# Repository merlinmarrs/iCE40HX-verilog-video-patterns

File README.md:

# Video FPGA Dev Board

A Lattice iCE40HX1K-based FPGA developement board for live-playable video experiments.

|                          |                          |
:-------------------------:|:-------------------------:
  | 

# Features :

- 9-key mechanical button interface
- Relatively low-cost, single board design
- HDMI and VGA out
- Reverse polarity and fuse protection

# Minimal BOM :

[Excel BOM Mouser / Digikey ](https://github.com/merlinmarrs/iCE40HX-verilog-video-patterns/tree/main/PCB%20files)

- 9x Mechanical keyboard keys
- 1x FPGA iCE40HX1K-TQ144
- 1x 100MHz clock oscillator
- 1x SRAM 2Mb 256Kx8
- 1x Flash N25Q032A13ESC40F
- 1x USB-C SMD 6 pin connector
- 1x 3.3V reg TLV73333PDBVT 
- 1x 1.2V reg TLV73312PDBVT
- 1x PFET
- 1x Resettable Fuse
- 1x D-SUB 15 connector
- 1x HDMI Connector 
- 50x 0.1µF capacitor 0805
- 50x  10kΩ, 1.8kΩ, 1kΩ, 470Ω, 270Ω, 120Ω resistors 0805
- 5x LEDs 0805
- 2x Dual-row headers

optional extras : (1x Raspberry Pi Zero, 1x Micro SD holder, 2x 10kΩ potentiometers, 1x fast op-amp, 1x 3.5mm audio jack, 1x dual SMD dip switch, 1x SMD pushbutton)

# PCB files

[KiCAD and Eagle PCBs](https://github.com/merlinmarrs/iCE40HX-verilog-video-patterns/tree/main/PCB%20files)

# HDL files

[Verilog, Pin constraints, and synthesized binaries ](https://github.com/merlinmarrs/iCE40HX-verilog-video-patterns/tree/main/verilog)

To compile and upload files :

[Yoysis Open-source Toolchain ](https://github.com/YosysHQ/yosys)

[iCEcube2 Toolchain](https://www.latticesemi.com/iCEcube2)

## Acknowledgements

Mike Field <hamster@snap.net.nz> for his minimalDVID_encoder.vhd : A quick and dirty DVI-D implementation

OLIMEX FPGA dev board https://github.com/OLIMEX/iCE40HX1K-EVB/tree/master

ALHAMBRA FPGA https://github.com/FPGAwars/Alhambra-II-FPGA/tree/master

HDL Bits https://hdlbits.01xz.net/wiki/Main_Page

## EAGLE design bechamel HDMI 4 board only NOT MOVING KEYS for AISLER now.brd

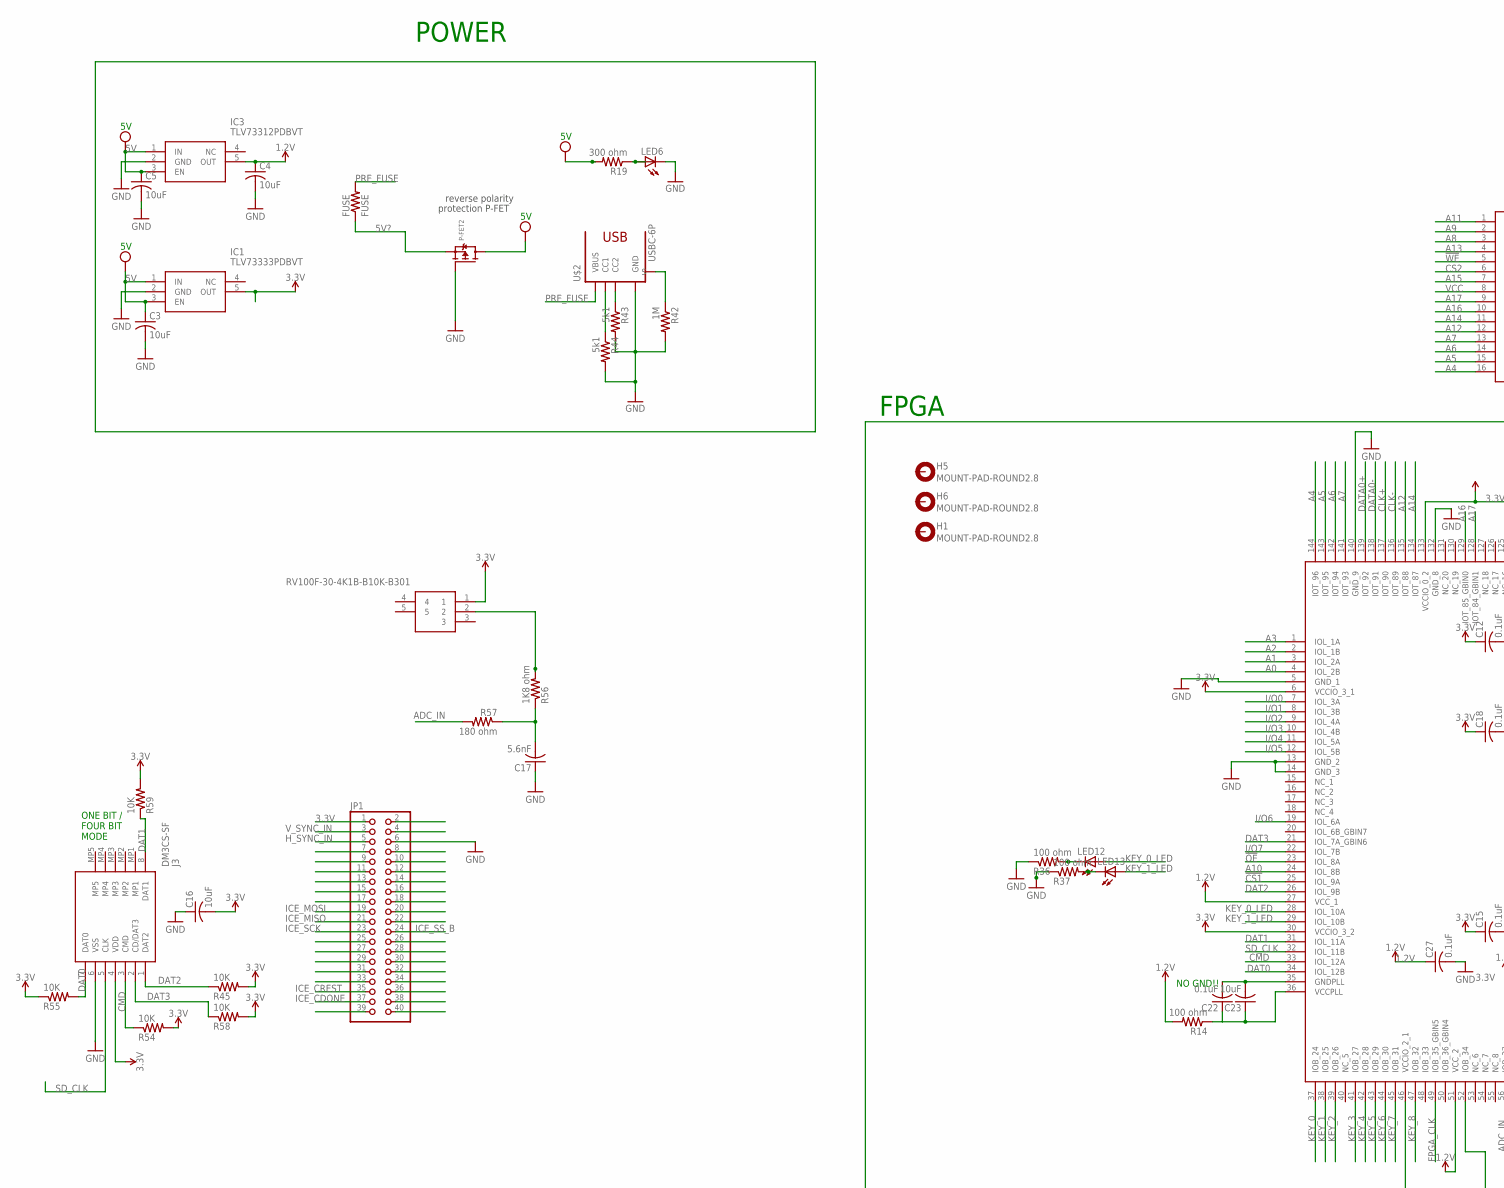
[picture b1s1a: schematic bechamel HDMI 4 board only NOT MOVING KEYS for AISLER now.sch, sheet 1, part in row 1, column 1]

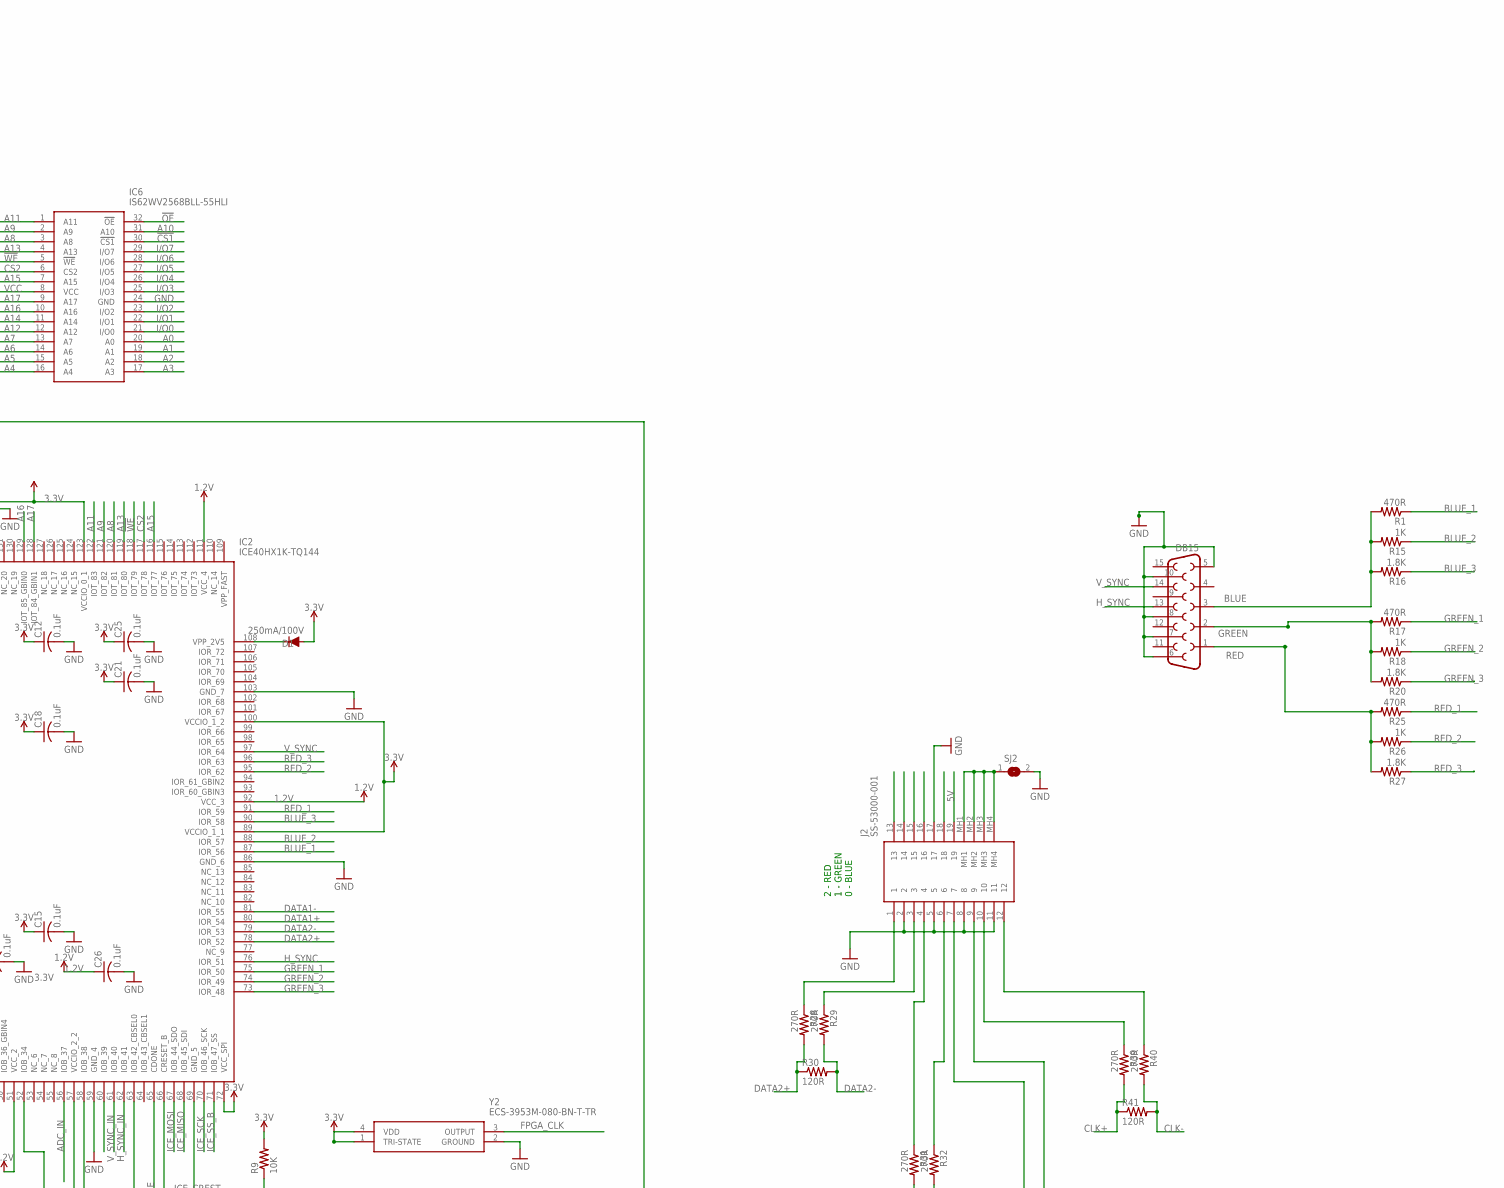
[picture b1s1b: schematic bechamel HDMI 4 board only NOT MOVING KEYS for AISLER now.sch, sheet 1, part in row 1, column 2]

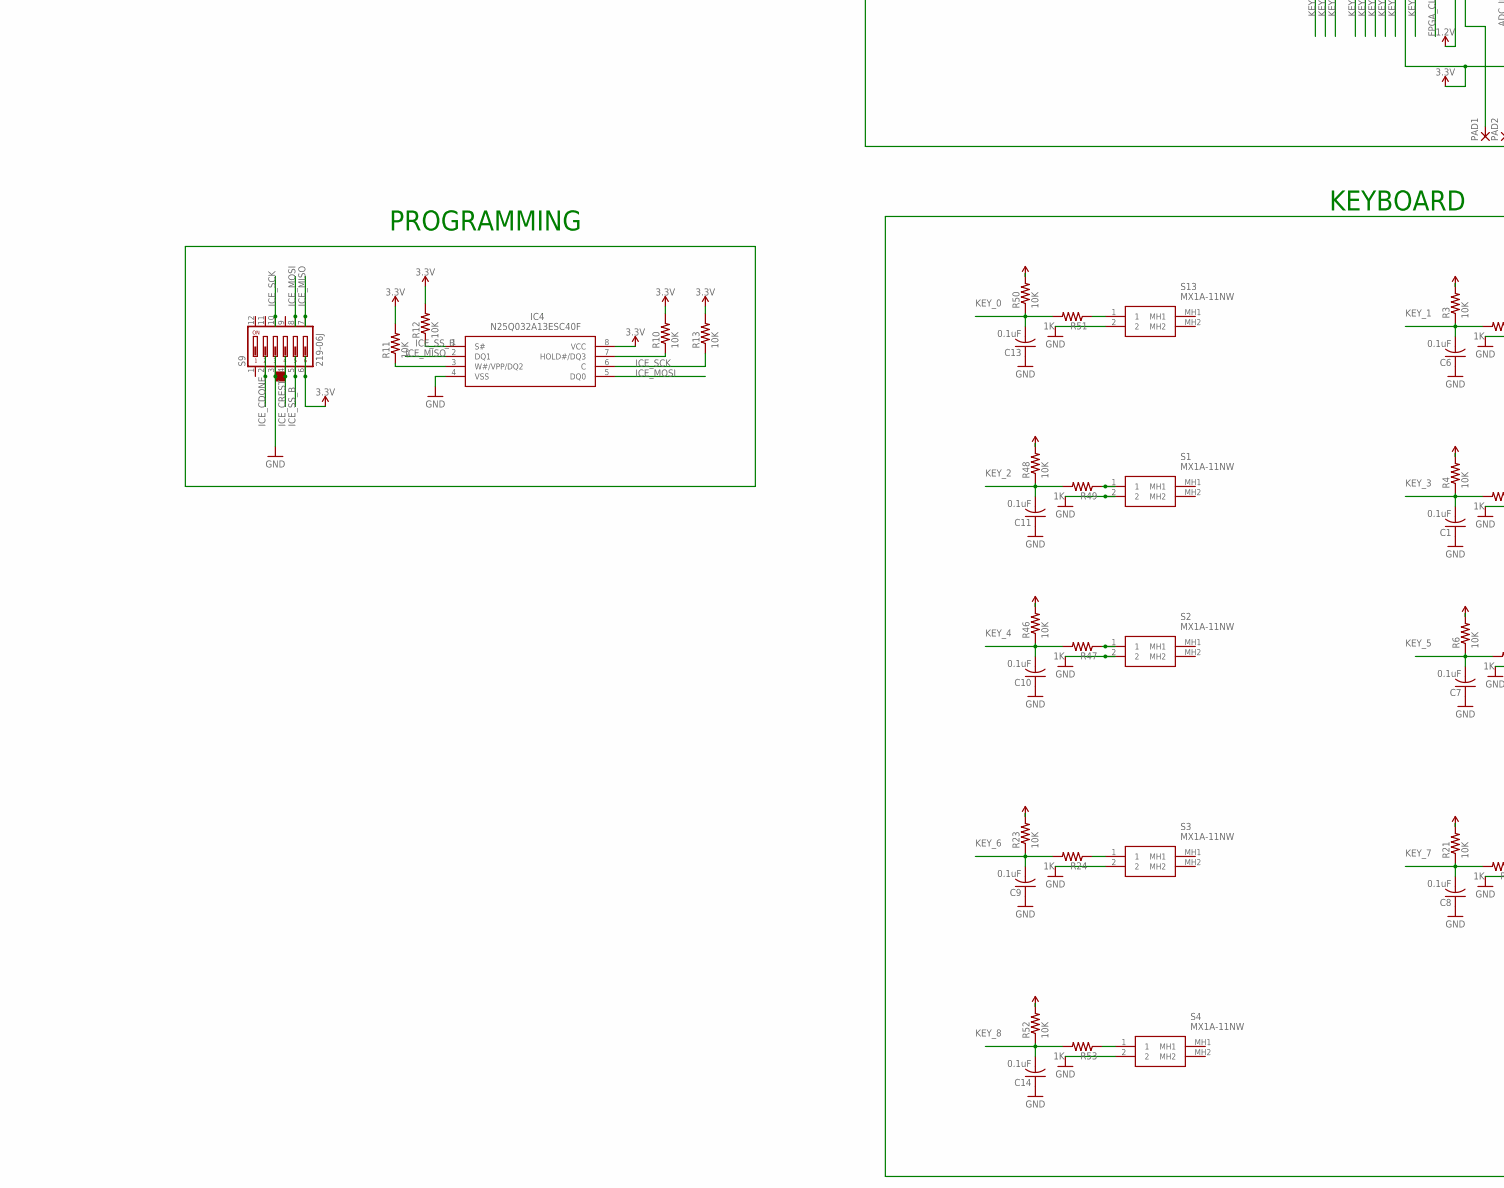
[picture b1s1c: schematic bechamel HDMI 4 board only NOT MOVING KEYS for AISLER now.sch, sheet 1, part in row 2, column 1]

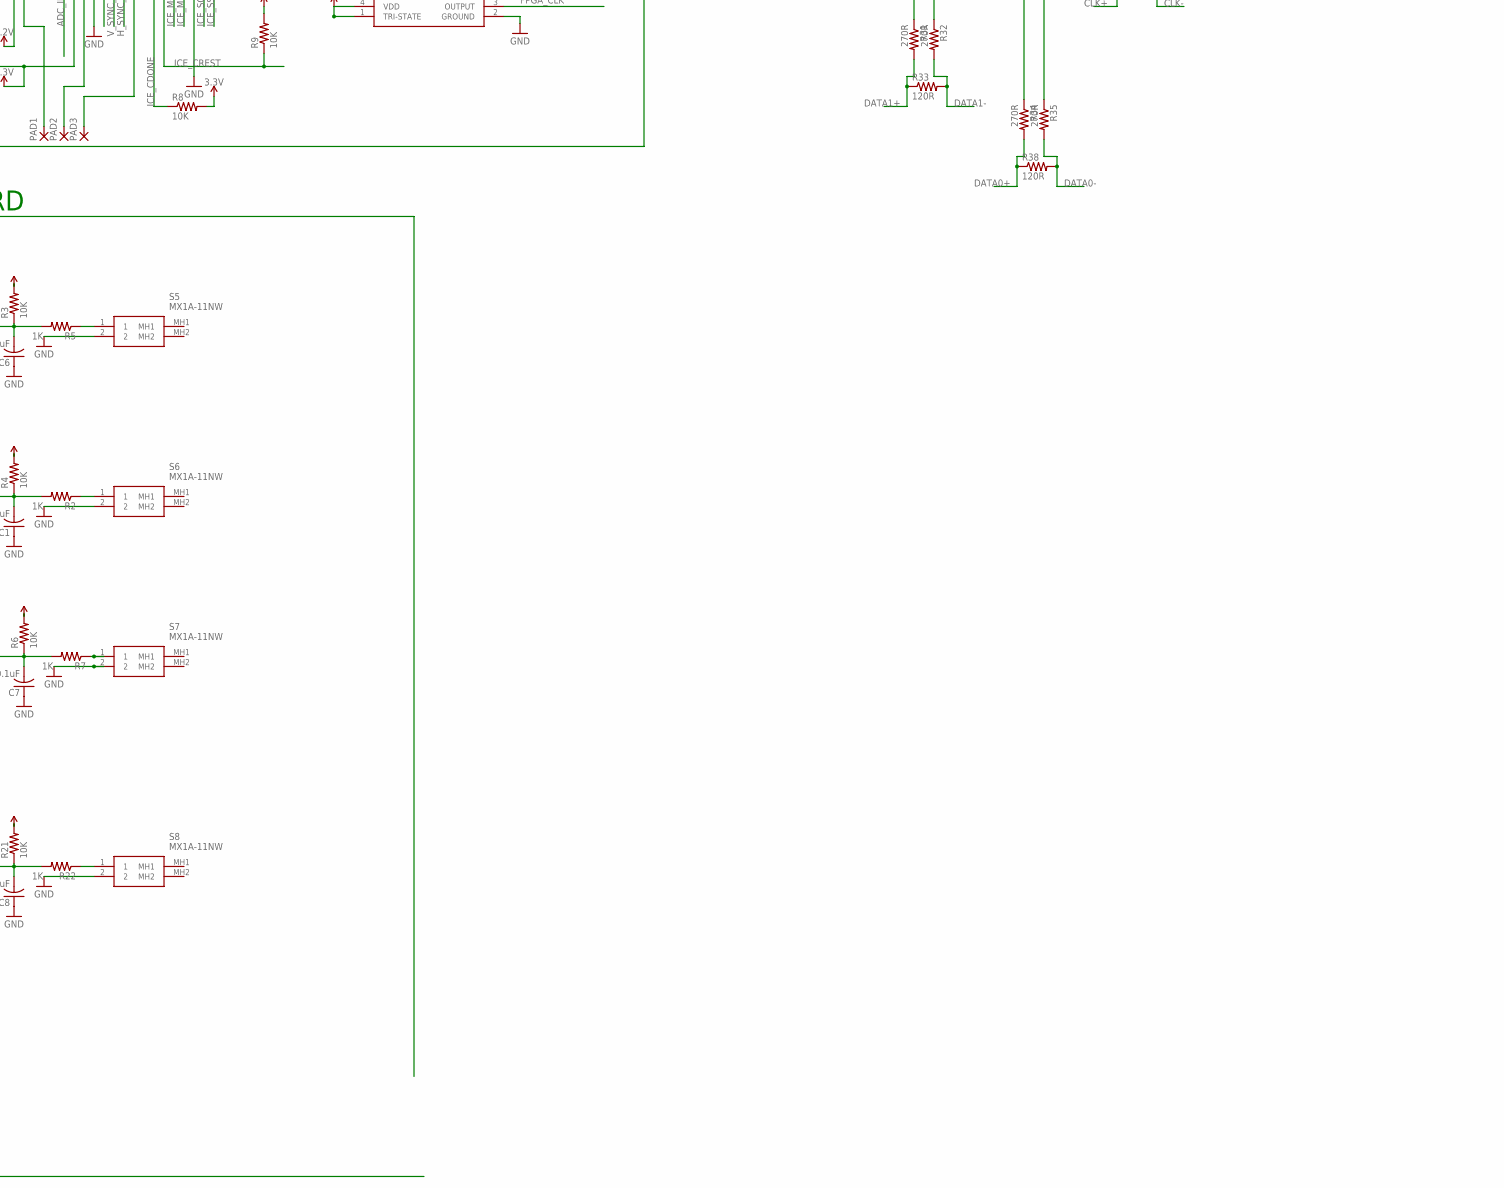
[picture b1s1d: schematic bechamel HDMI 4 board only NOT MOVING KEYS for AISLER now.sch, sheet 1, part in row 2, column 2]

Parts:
C1, C6, C7, C8, C9, C10, C11, C12, C13, C14, C15, C18, C21, C22, C25, C26, C27: 0.1uF; C0805
C3, C4, C5, C16, C23: 10uF; C0805
C17: 5.6nF; C0805
D1: 250mA/100V; SOD-323
FUSE: FUSE; R0805
H1, H5, H6: MOUNT-PAD-ROUND2.8; 2,8-PAD
IC1: TLV73333PDBVT; SOT95P280X145-5N
IC2: ICE40HX1K-TQ144; QFP50P2200X2200X160-144N
IC3: TLV73312PDBVT; SOT95P280X145-5N
IC4: N25Q032A13ESC40F; SOIC127P600X175-8N
IC6: IS62WV2568BLL-55HLI; SOP50P1340X125-32N
J2: SS-53000-001; SS53000001
J3: DM3CS-SF; DM3CSSF
JP1: PINHD-2X20; 2X20
LED6, LED12, LED13: LEDCHIPLED_0805; CHIPLED_0805
P-FET2: MOSFET-PWIDE; SOT23-WIDE
PAD1, PAD2, PAD3: SMD2; SMD1,27-2,54
R1, R17, R25: 470R; R0805
R2, R5, R7, R15, R18, R22, R24, R26, R47, R49, R51, R53: 1K; R0805
R3, R4, R6, R8, R9, R10, R11, R12, R13, R21, R23, R45, R46, R48, R50, R52, R54, R55, R58, R59: 10K; R0805
R14, R36, R37: 100 ohm; R0805
R16, R20, R27: 1.8K; R0805
R19: 300 ohm; R0805
R28, R29, R31, R32, R34, R35, R39, R40: 270R; R0805
R30, R33, R38, R41: 120R; R0805
R42: 1M; R0805
R43, R44: 5k1; R0805
R56: 1K8 ohm; R0805
R57: 180 ohm; R0805
S1, S2, S3, S4, S5, S6, S7, S8, S13: MX1A-11NW; MX1A11NW
S9: 219-06J; CTS-219-06J
SJ2: SJ
U$1: DB15
U$2: USBC-6P; USCX-06FX-XXMX-01
VR1: RV100F-30-4K1B-B10K-B301; RV100F304K1BB10KB301
Y2: ECS-3953M-080-BN-T-TR; ECS3953M080BNTTR

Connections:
1.2V: C4.1, C26.1, C27.1, IC2.27 (VCC_1), IC2.51 (VCC_2), IC2.92 (VCC_3), IC2.111 (VCC_4), IC3.5 (OUT), R14.2
3.3V: C12.1, C15.1, C16.2, C18.1, C21.1, C25.1, D1.A, IC1.5 (OUT), IC2.6 (VCCIO_3_1), IC2.30 (VCCIO_3_2), IC2.46 (VCCIO_2_1), IC2.57 (VCCIO_2_2), IC2.72 (VCC_SPI), IC2.89 (VCCIO_1_1), IC2.100 (VCCIO_1_2), IC2.123 (VCCIO_0_1), IC2.133 (VCCIO_0_2), IC4.8 (VCC), J3.4 (VDD), JP1.1, R3.2, R4.2, R6.2, R8.2, R9.2, R10.2, R11.2, R12.2, R13.2, R21.2, R23.2, R45.2, R46.2, R48.2, R50.2, R52.2, R54.2, R55.1, R58.2, R59.2, S9.6, VR1.1, Y2.1 (TRI-STATE), Y2.4 (VDD)
5V: C3.1, C5.1, IC1.1 (IN), IC1.3 (EN), IC3.1 (IN), IC3.3 (EN), J2.18, P-FET2.3 (D), R19.2
5V?: FUSE.1, P-FET2.2 (S)
!CS1: IC2.25 (IOL_9A), IC6.30 (!CS1)
!OE: IC2.23 (IOL_8A), IC6.32 (!OE)
!WE: IC2.118 (IOT_79), IC6.5 (!WE)
A0: IC2.4 (IOL_2B), IC6.20 (A0)
A1: IC2.3 (IOL_2A), IC6.19 (A1)
A2: IC2.2 (IOL_1B), IC6.18 (A2)
A3: IC2.1 (IOL_1A), IC6.17 (A3)
A4: IC2.144 (IOT_96), IC6.16 (A4)
A5: IC2.143 (IOT_95), IC6.15 (A5)
A6: IC2.142 (IOT_94), IC6.14 (A6)
A7: IC2.141 (IOT_93), IC6.13 (A7)
A8: IC2.120 (IOT_81), IC6.3 (A8)
A9: IC2.121 (IOT_82), IC6.2 (A9)
A10: IC2.24 (IOL_8B), IC6.31 (A10)
A11: IC2.122 (IOT_83), IC6.1 (A11)
A12: IC2.135 (IOT_88), IC6.12 (A12)
A13: IC2.119 (IOT_80), IC6.4 (A13)
A14: IC2.134 (IOT_87), IC6.11 (A14)
A15: IC2.116 (IOT_77), IC6.7 (A15)
A16: IC2.129 (IOT_85_GBIN0), IC6.10 (A16)
A17: IC2.128 (IOT_84_GBIN1), IC6.9 (A17)
ADC_IN: IC2.56 (IOB_37), R57.2
BLUE: R1.2, R15.2, R16.2, U$1.3
BLUE_1: IC2.87 (IOR_56), R1.1
BLUE_2: IC2.88 (IOR_57), R15.1
BLUE_3: IC2.90 (IOR_58), R16.1
CLK+: IC2.137 (IOT_90), R39.2, R41.1
CLK-: IC2.136 (IOT_89), R40.2, R41.2
CMD: IC2.33 (IOL_12A), J3.3 (CMD), R54.1
CS2: IC2.117 (IOT_78), IC6.6 (CS2)
DAT0: IC2.34 (IOL_12B), J3.7 (DAT0), R55.2
DAT1: IC2.31 (IOL_11A), J3.8 (DAT1), R59.1
DAT2: IC2.26 (IOL_9B), J3.1 (DAT2), R45.1
DAT3: IC2.21 (IOL_7A_GBIN6), J3.2 (CD/DAT3), R58.1
DATA0+: IC2.139 (IOT_92), R34.2, R38.1
DATA0-: IC2.138 (IOT_91), R35.2, R38.2
DATA1+: IC2.80 (IOR_54), R31.2, R33.1
DATA1-: IC2.81 (IOR_55), R32.2, R33.2
DATA2+: IC2.78 (IOR_52), R28.2, R30.1
DATA2-: IC2.79 (IOR_53), R29.2, R30.2
FPGA_CLK: IC2.49 (IOB_35_GBIN5), Y2.3 (OUTPUT)
GND: C1.1, C3.2, C4.2, C5.2, C6.1, C7.1, C8.1, C9.1, C10.1, C11.1, C12.2, C13.1, C14.1, C15.2, C16.1, C17.1, C18.2, C21.2, C25.2, C26.2, C27.2, IC1.2 (GND), IC2.5 (GND_1), IC2.13 (GND_2), IC2.14 (GND_3), IC2.59 (GND_4), IC2.69 (GND_5), IC2.86 (GND_6), IC2.103 (GND_7), IC2.132 (GND_8), IC2.140 (GND_9), IC3.2 (GND), IC4.4 (VSS), IC6.24 (GND), J2.2, J2.5, J2.8, J2.11, J2.17, J3.6 (VSS), JP1.6, LED6.C, P-FET2.1 (G), R36.1, R37.1, R42.2, R43.2, R44.2, S1.2, S2.2, S3.2, S4.2, S5.2, S6.2, S7.2, S8.2, S9.3, S13.2, SJ2.2, U$1.5, U$1.6, U$1.7, U$1.8, U$1.10, U$2.GND1 (GND), U$2.GND2 (GND), Y2.2 (GROUND)
GREEN: R17.2, R18.2, R20.2, U$1.2
GREEN_1: IC2.75 (IOR_50), R17.1
GREEN_2: IC2.74 (IOR_49), R18.1
GREEN_3: IC2.73 (IOR_48), R20.1
H_SYNC: IC2.76 (IOR_51), U$1.13
H_SYNC_IN: IC2.62 (IOB_41), JP1.5
I/O0: IC2.7 (IOL_3A), IC6.21 (I/O0)
I/O1: IC2.8 (IOL_3B), IC6.22 (I/O1)
I/O2: IC2.9 (IOL_4A), IC6.23 (I/O2)
I/O3: IC2.10 (IOL_4B), IC6.25 (I/O3)
I/O4: IC2.11 (IOL_5A), IC6.26 (I/O4)
I/O5: IC2.12 (IOL_5B), IC6.27 (I/O5)
I/O6: IC2.19 (IOL_6A), IC6.28 (I/O6)
I/O7: IC2.22 (IOL_7B), IC6.29 (I/O7)
ICE_CDONE: IC2.65 (CDONE), JP1.37, R8.1, S9.2
ICE_CREST: IC2.66 (CRESET_B), JP1.35, R9.1, S9.4
ICE_MISO: IC2.68 (IOB_45_SDI), IC4.2 (DQ1), JP1.21, S9.7
ICE_MOSI: IC2.67 (IOB_44_SDO), IC4.5 (DQ0), JP1.19, S9.8
ICE_SCK: IC2.70 (IOB_46_SCK), IC4.6 (C), JP1.23, R13.1, S9.10
ICE_SS_B: IC2.71 (IOB_47_SS), IC4.1 (S#), JP1.24, R12.1, S9.5
KEY_0: C13.2, IC2.37 (IOB_24), R50.1, R51.2
KEY_0_LED: IC2.28 (IOL_10A), LED12.A
KEY_1: C6.2, IC2.38 (IOB_25), R3.1, R5.2
KEY_1_LED: IC2.29 (IOL_10B), LED13.A
KEY_2: C11.2, IC2.39 (IOB_26), R48.1, R49.2
KEY_3: C1.2, IC2.41 (IOB_27), R2.2, R4.1
KEY_4: C10.2, IC2.42 (IOB_28), R46.1, R47.2
KEY_5: C7.2, IC2.43 (IOB_29), R6.1, R7.2
KEY_6: C9.2, IC2.44 (IOB_30), R23.1, R24.2
KEY_7: C8.2, IC2.45 (IOB_31), R21.1, R22.2
KEY_8: C14.2, IC2.47 (IOB_32), R52.1, R53.2
unnamed: IC4.7 (HOLD#/DQ3), R10.1
unnamed: LED6.A, R19.1
unnamed: IC4.3 (W#/VPP/DQ2), R11.1
unnamed: R43.1, U$2.CC2
unnamed: D1.C, IC2.108 (VPP_2V5)
unnamed: C22.2, C23.2, IC2.35 (GNDPLL)
unnamed: C22.1, C23.1, IC2.36 (VCCPLL), R14.1
unnamed: R42.1, U$2.SHIELD1 (S), U$2.SHIELD2 (S), U$2.SHIELD3 (S), U$2.SHIELD4 (S)
unnamed: R56.2, VR1.2
unnamed: J2.1, R28.1
unnamed: R44.1, U$2.CC1
unnamed: J2.MH1, J2.MH2, J2.MH3, J2.MH4, SJ2.1
unnamed: C17.2, R56.1, R57.1
unnamed: J2.3, R29.1
unnamed: J2.4, R31.1
unnamed: LED12.C, R36.2
unnamed: LED13.C, R37.2
unnamed: J2.6, R32.1
unnamed: IC2.52 (IOB_34), PAD1.1
unnamed: J2.7, R34.1
unnamed: J2.9, R35.1
unnamed: J2.10, R39.1
unnamed: J2.12, R40.1
unnamed: R2.1, S6.1
unnamed: R5.1, S5.1
unnamed: R7.1, S7.1
unnamed: R22.1, S8.1
unnamed: R24.1, S3.1
unnamed: R47.1, S2.1
unnamed: R49.1, S1.1
unnamed: R51.1, S13.1
unnamed: R53.1, S4.1
unnamed: IC2.58 (IOB_38), PAD2.1
unnamed: IC2.63 (IOB_42_CBSEL0), PAD3.1
PRE_FUSE: FUSE.2, U$2.VBUS1 (VBUS), U$2.VBUS2 (VBUS)
RED: R25.2, R26.2, R27.2, U$1.1
RED_1: IC2.91 (IOR_59), R25.1
RED_2: IC2.95 (IOR_62), R26.1
RED_3: IC2.96 (IOR_63), R27.1
SD_CLK: IC2.32 (IOL_11B), J3.5 (CLK)
VCC: IC6.8 (VCC)
V_SYNC: IC2.97 (IOR_64), U$1.14
V_SYNC_IN: IC2.61 (IOB_40), JP1.3

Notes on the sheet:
NO GND!!
POWER
reverse polarity
protection P-FET
PROGRAMMING
FPGA
KEYBOARD
2 - RED 1 - GREEN 0 - BLUE
ONE BIT / FOUR BIT MODE

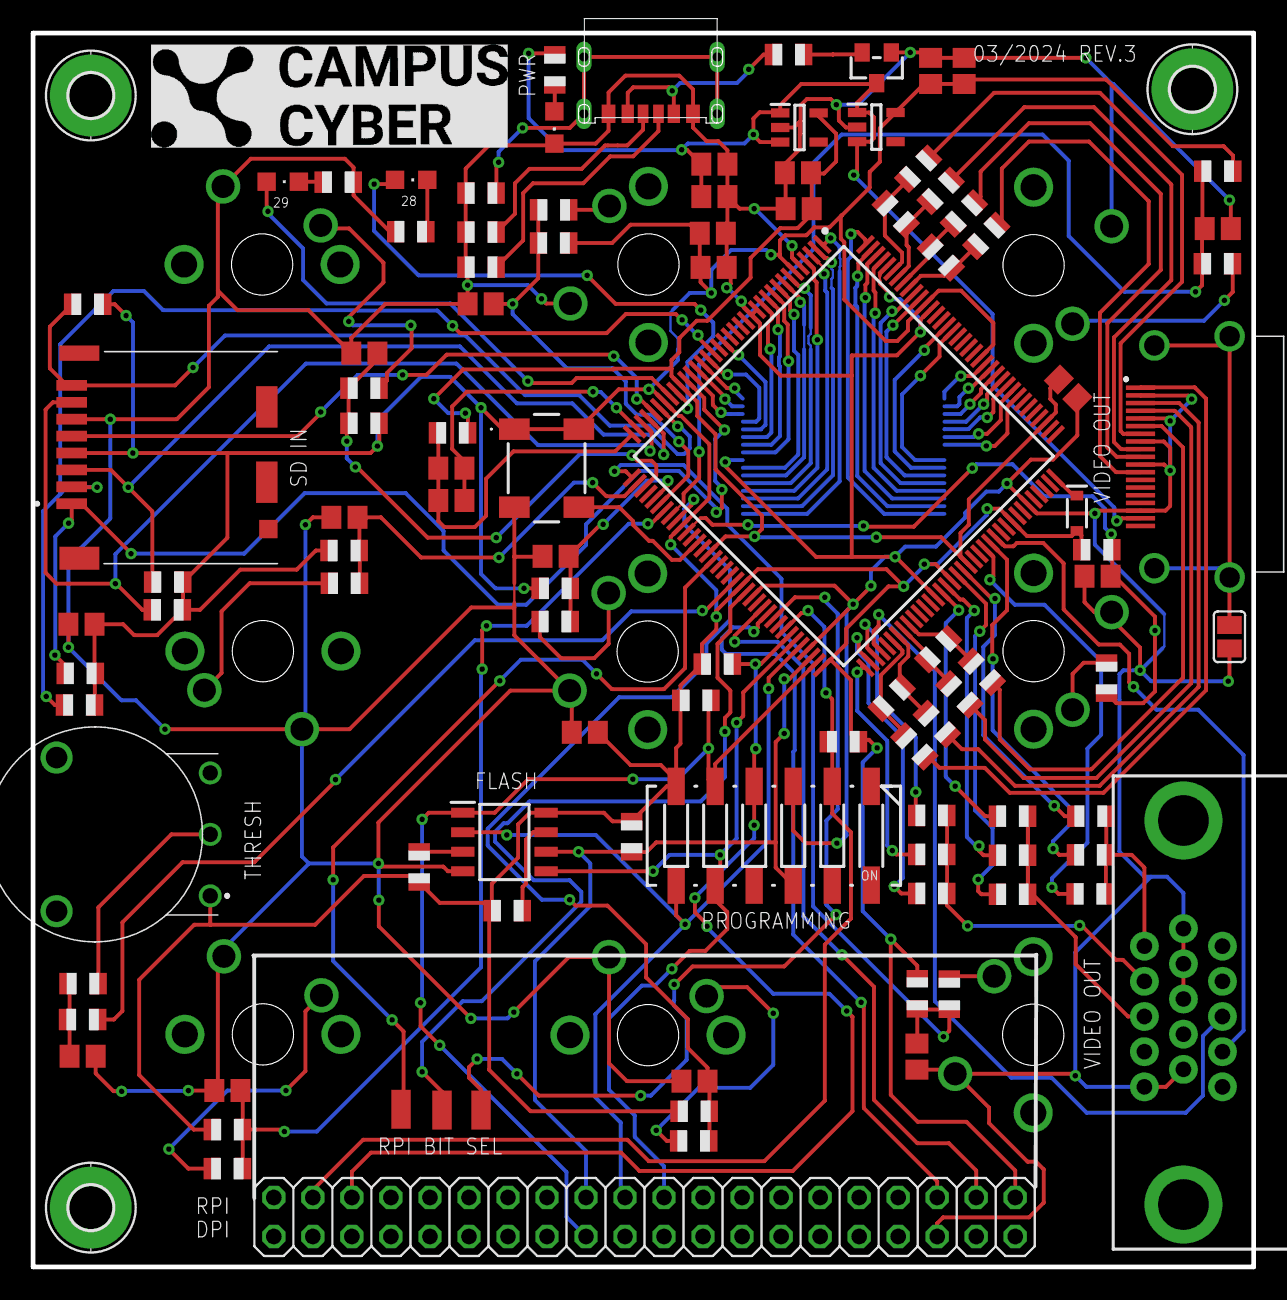
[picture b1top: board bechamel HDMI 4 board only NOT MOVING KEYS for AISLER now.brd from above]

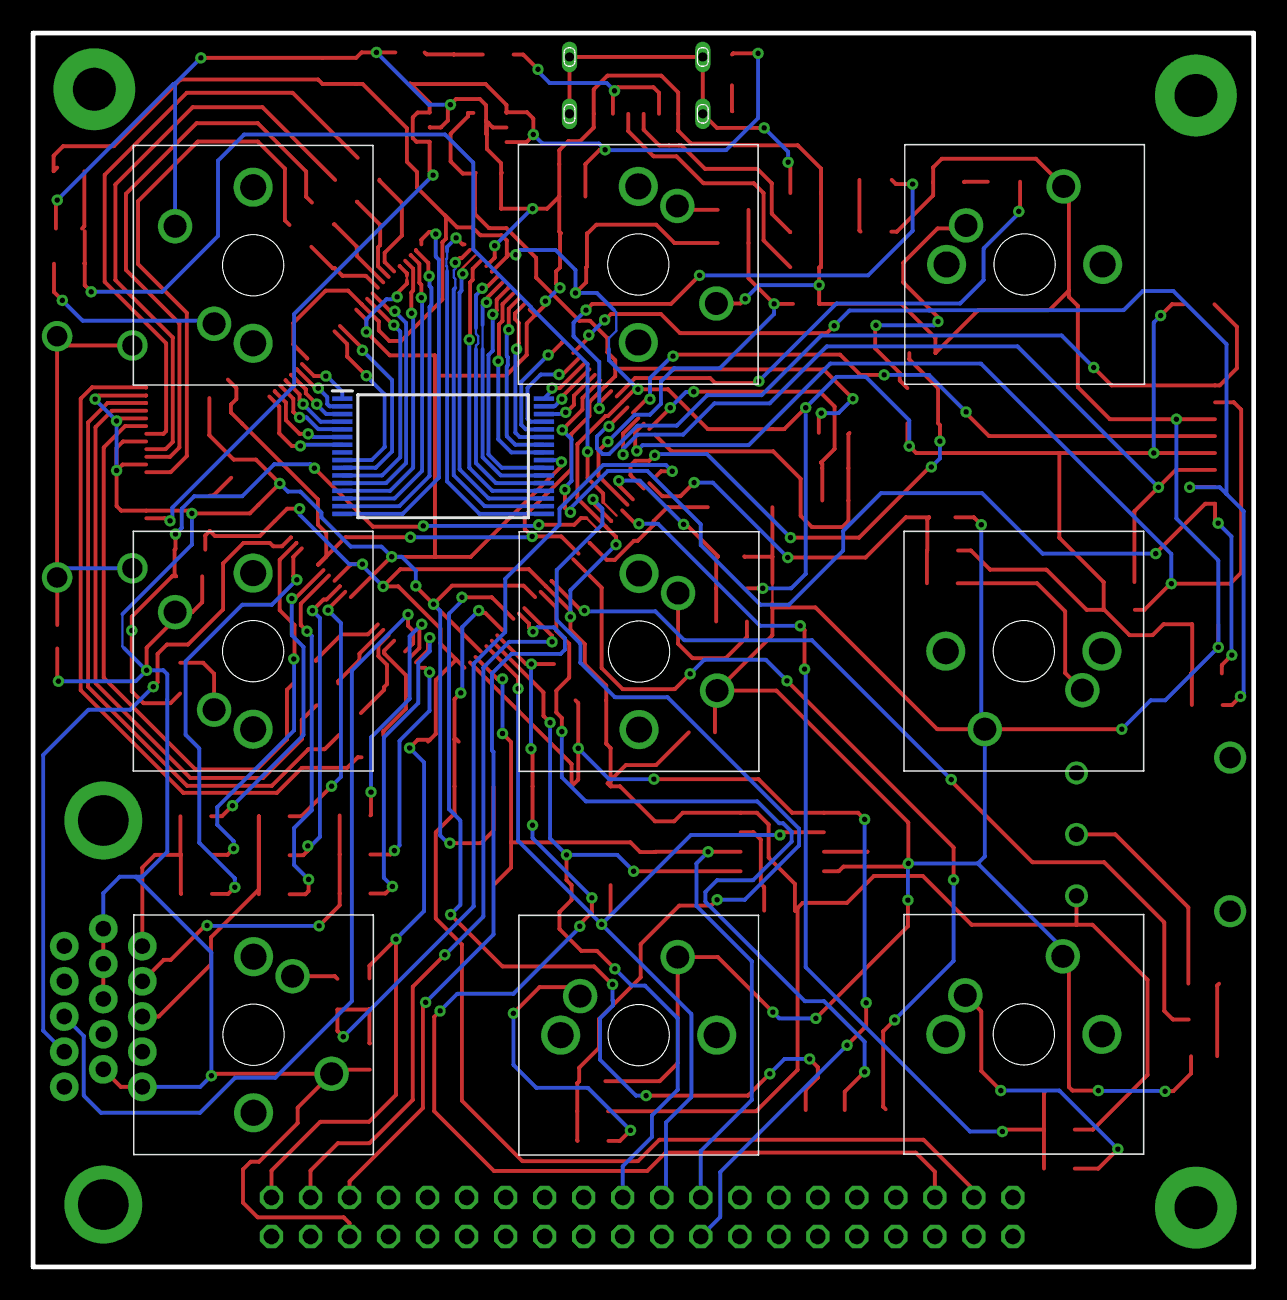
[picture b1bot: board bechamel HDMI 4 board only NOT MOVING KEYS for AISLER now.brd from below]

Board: 2 copper layers, 79.5 x 80.3 mm, 117 parts (10 on the bottom side), 119 nets.

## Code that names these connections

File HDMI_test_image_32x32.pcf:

set_io hdmi_p[0] 139 -io_std SB_LVCMOS
set_io hdmi_p[2] 78 -io_std SB_LVCMOS
set_io hdmi_p[1] 80 -io_std SB_LVCMOS
set_io hdmi_p[3] 137 -io_std SB_LVCMOS

set_io hdmi_n[0] 138 -io_std SB_LVCMOS
set_io hdmi_n[2] 79 -io_std SB_LVCMOS
set_io hdmi_n[1] 81 -io_std SB_LVCMOS
set_io hdmi_n[3] 136 -io_std SB_LVCMOS

set_io key[0] 37
set_io key[1] 38
set_io key[2] 39
set_io key[3] 41
set_io key[4] 42
set_io key[5] 43
set_io key[6] 44
set_io key[7] 45
set_io rec 47

set_io SCK 32
set_io CMD 33

set_io LED1 29
set_io LED5 28

set_io reset 66

set_io clk100 49

set_io b_in 62

set_io v_sync 97 //for vga
set_io h_sync 76 //for vga

set_io io[0] 7
set_io io[1] 8
set_io io[2] 9
set_io io[3] 10
set_io io[4] 11
set_io io[5] 12
set_io io[6] 19
set_io io[7] 22

set_io addr[0] 4
set_io addr[1] 3
set_io addr[2] 2
set_io addr[3] 1
set_io addr[4] 144
set_io addr[5] 143
set_io addr[6] 142
set_io addr[7] 141
set_io addr[8] 120
set_io addr[9] 121
set_io addr[10] 24
set_io addr[11] 122
set_io addr[12] 135
set_io addr[13] 119
set_io addr[14] 134
set_io addr[15] 116
set_io addr[16] 129
set_io addr[17] 128


set_io cs 25
set_io oe 23
set_io we 118

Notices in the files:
README.md:
License: MIT
parts and their libraries:
SparkFun-DiscreteSemi: Licensing: Creative Commons ShareAlike 4.0 International - https://creativecommons.org/licenses/by-sa/4.0
microbuilder: This work is placed in the public domain, and may be freely used for commercial and non-commercial work with the following conditions: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
